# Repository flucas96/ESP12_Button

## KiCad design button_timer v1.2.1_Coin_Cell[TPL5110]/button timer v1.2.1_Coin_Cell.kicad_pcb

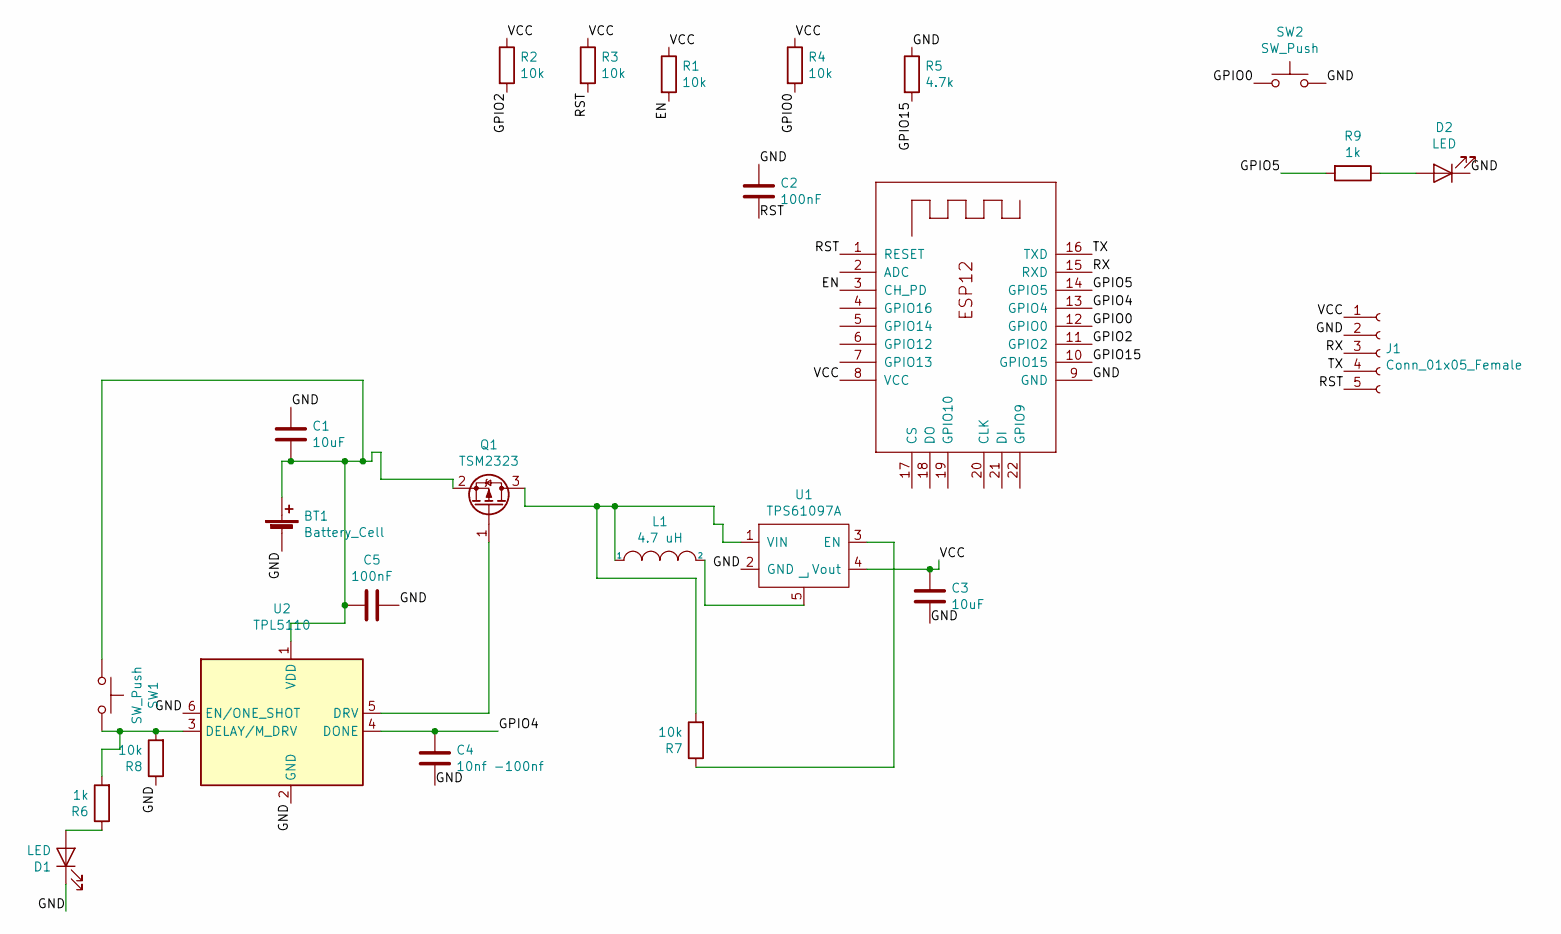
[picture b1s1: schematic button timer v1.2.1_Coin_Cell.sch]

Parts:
BT1: Battery_Cell; BatteryHolder_Keystone_1058_1x2032
C1, C3: 10uF; C_0805_2012handsodermod
C2, C5: 100nF; C_0805_2012handsodermod
C4: 10nf -100nf; C_0402_1005Metric_Pad0.74x0.62mm_HandSoldermod
D1: LED; LED_1206_3216Metric_Castellated
D2: LED; LED_0805_2012Metric_Castellated
J1: Conn_01x05_Female; PinSocket_1x05_P2.54mm_Vertical_mod
L1: 4.7 uH; SMD-1210_Pol_inductor
Q1: TSM2323; SOT-23
R1, R2, R3, R4, R7, R8: 10k; R_0805_2012handsoldermod
R5: 4.7k; R_0805_2012handsoldermod
R6, R9: 1k; R_0805_2012handsoldermod
SW1: SW_Push; SW_PUSH_6mm_H8mm_mod
SW2: SW_Push; SW_SPST_B3U-1000P_mod
U1: TPS61097A; SOT-23-5_HandSolderingmod
U2: TPL5110; SOT-23-6
X1: ESP-12E; ESP-12Elesssilk

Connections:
/EN: R1.2, X1.3 (CH_PD)
/GND: BT1.2 (-), C1.1, C2.1, C3.2, C4.2, C5.1, D1.1 (K), D2.1 (K), J1.2, R5.1, R8.1, SW2.2, U1.2 (GND), U2.2 (GND), U2.6 (EN/ONE_SHOT), X1.9 (GND); also elsewhere on the board
/GPIO0: R4.2, SW2.1, X1.12 (GPIO0)
/GPIO2: R2.2, X1.11 (GPIO2)
/GPIO4: C4.1, U2.4 (DONE), X1.13 (GPIO4)
/GPIO5: R9.2, X1.14 (GPIO5)
/GPIO15: R5.2, X1.10 (GPIO15)
/RST: C2.2, J1.5, R3.2, X1.1 (RESET)
/RX: J1.3, X1.15 (RXD)
/TX: J1.4, X1.16 (TXD)
/VCC: C3.1, J1.1, R1.1, R2.1, R3.1, R4.1, U1.4 (Vout), X1.8 (VCC); also elsewhere on the board
unnamed: BT1.1 (+), C1.2, C5.2, Q1.2 (S), SW1.1, U2.1 (VDD)
unnamed: D1.2 (A), R6.1
unnamed: D2.2 (A), R9.1
unnamed: L1.1, Q1.3 (D), R7.2, U1.1 (VIN)
unnamed: L1.2, U1.5 (L)
unnamed: Q1.1 (G), U2.5 (DRV)
unnamed: R6.2, R8.2, SW1.2, U2.3 (DELAY/M_DRV)
unnamed: R7.1, U1.3 (EN)

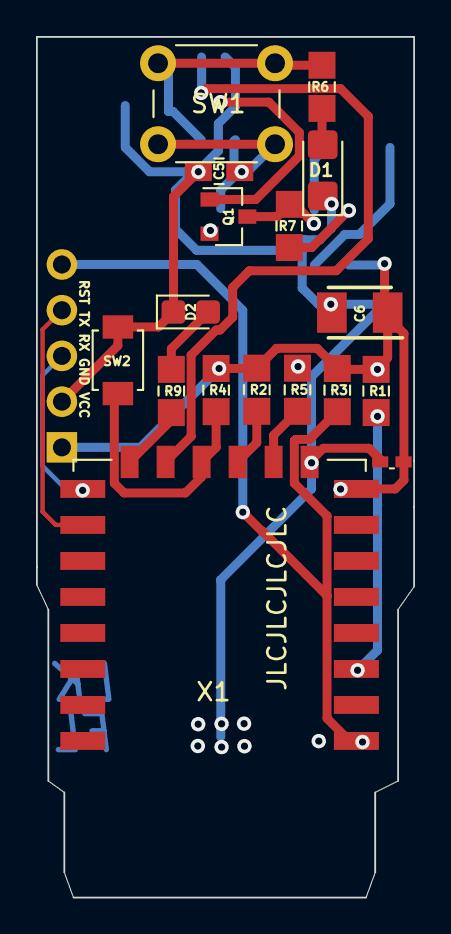
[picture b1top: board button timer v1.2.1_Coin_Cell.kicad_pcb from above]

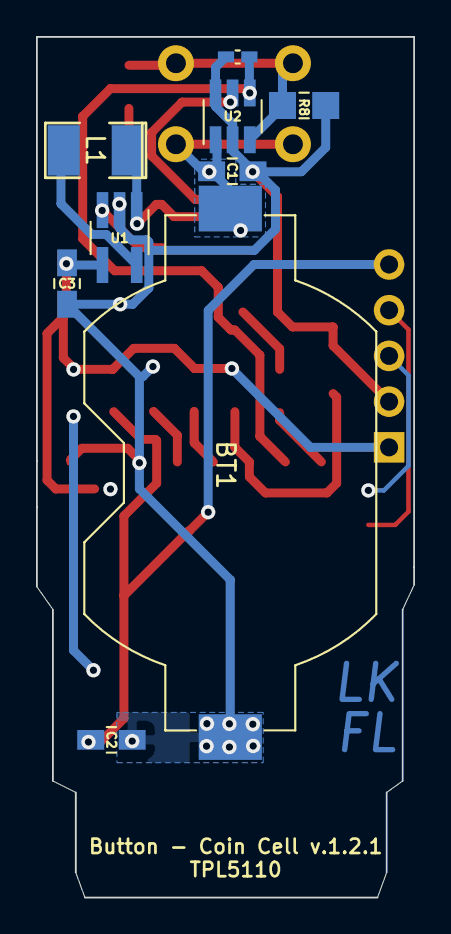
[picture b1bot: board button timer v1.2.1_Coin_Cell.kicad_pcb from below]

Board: 2 copper layers, 21.0 x 47.8 mm, 27 parts (9 on the bottom side), 19 nets.

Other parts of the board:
C6: T495B476K006ATE450; CAPPM3528X210N
C7: 100nF; C_0402_1005Metric_Pad0.74x0.62mm_HandSoldermod

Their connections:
/GND: C6.2, C7.2; also elsewhere on the board
/VCC: C6.1, C7.1; also elsewhere on the board
